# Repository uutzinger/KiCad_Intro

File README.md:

# KiCad Introduction

Created for BME210 Sophomore Design Course

Urs Utzinger, 2026

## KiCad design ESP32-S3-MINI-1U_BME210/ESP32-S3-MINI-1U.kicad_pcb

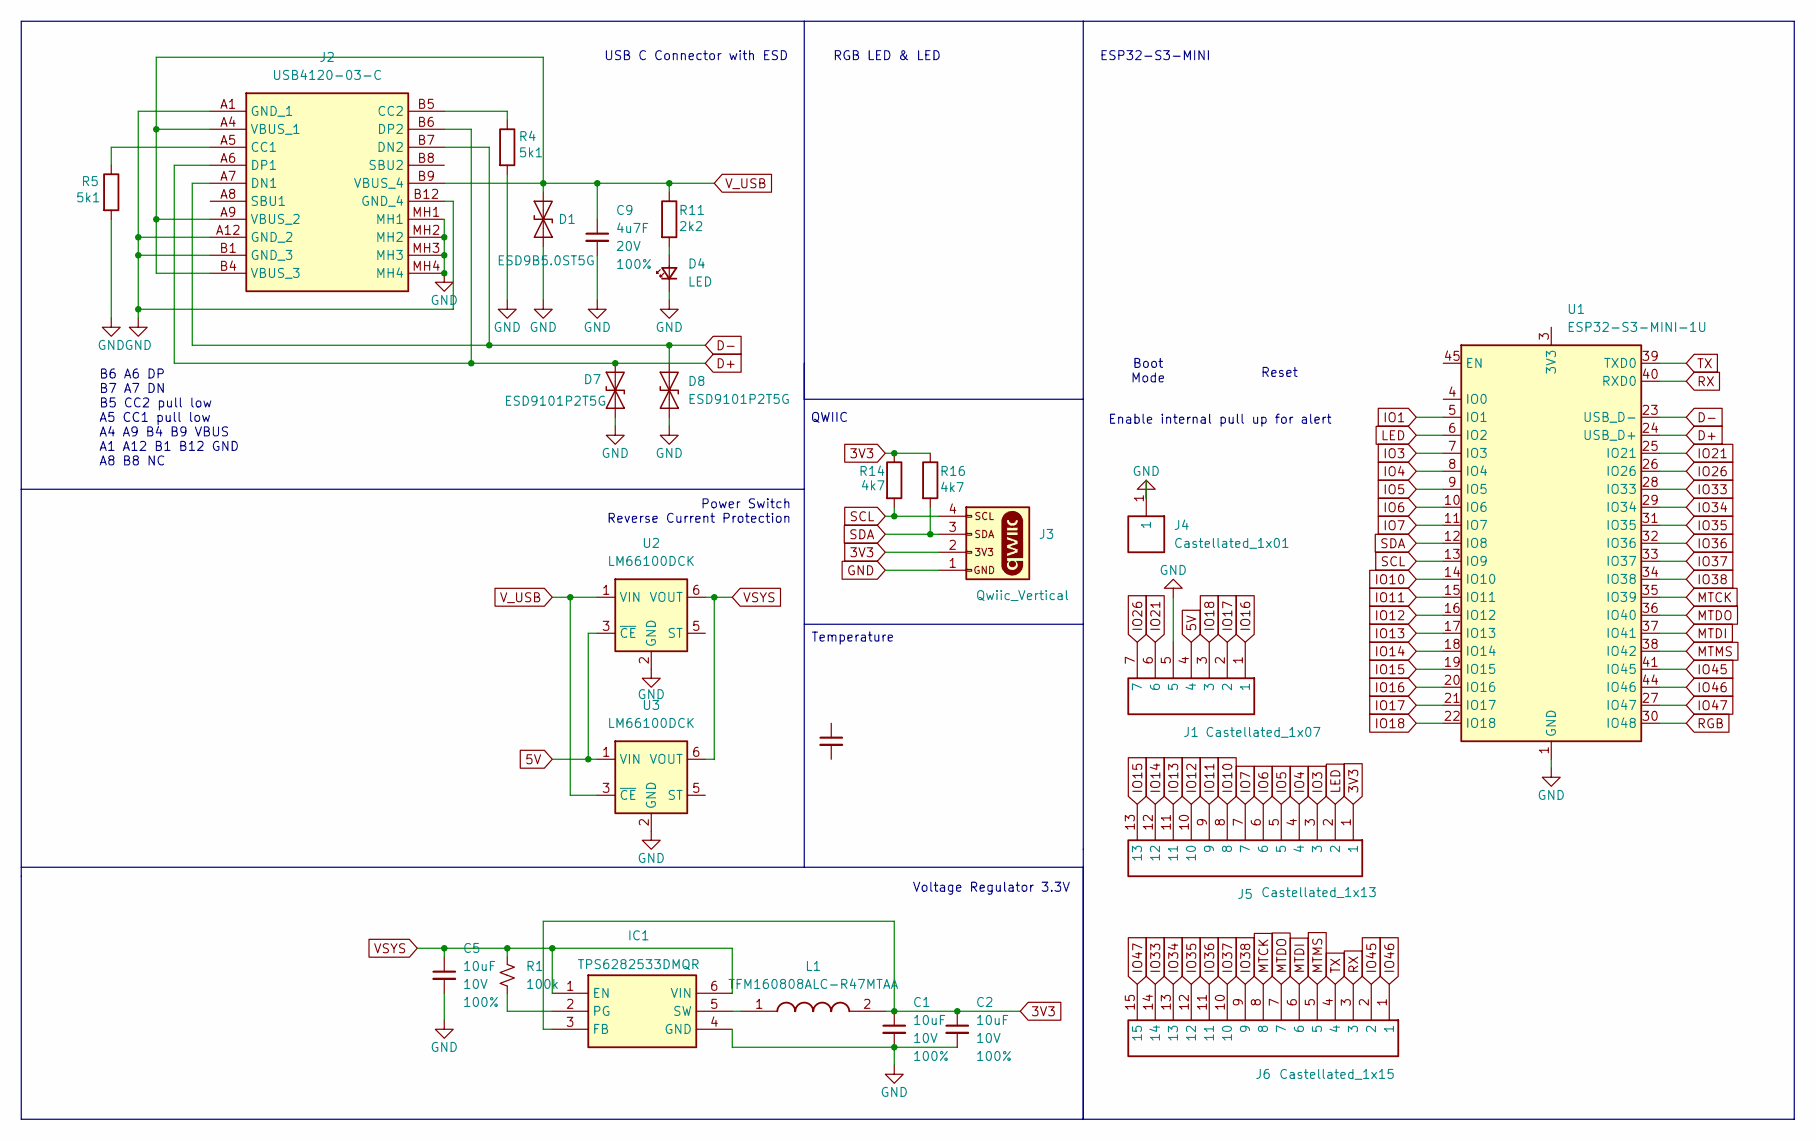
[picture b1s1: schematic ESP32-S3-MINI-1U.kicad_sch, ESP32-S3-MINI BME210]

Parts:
C1, C2, C5: 10uF; C_0402_1005Metric; Voltage 10V; Tolerance 100%
C9: 4u7F; C_0402_1005Metric; Voltage 20V; Tolerance 100%
C14: 10nF; C_0402_1005Metric; Voltage 50V; Tolerance 10%
D1: ESD9B5.0ST5G; D_SOD-923
D4: LED; LED_0402_1005Metric
D7, D8: ESD9101P2T5G; D_SOD-923
IC1: TPS6282533DMQR; Manufacturer_Part_Number TPS6282533DMQR; Mouser Part Number 595-TPS6282533DMQR
J1: Castellated_1x07; Castellated_1x07_P2.54mm_D0.80mm
J2: USB4120-03-C; USB412003C; Manufacturer_Part_Number USB4120-03-C; Mouser Part Number 640-USB4120-03-C
J3: Qwiic_Vertical; JST_1x04_P1.0mm_Vertical_SMD
J4: Castellated_1x01; Castellated_1x01_P2.54mm_D0.80mm
J5: Castellated_1x13; Castellated_1x13_P2.54mm_D0.80mm
J6: Castellated_1x15; Castellated_1x15_P2.54mm_D0.80mm
L1: TFM160808ALC-R47MTAA; INDC1608X75N; Manufacturer_Part_Number TFM160808ALC-R47MTAA; Mouser Part Number 810-TFM160808ALCR47A
R1: 100k; R_0402_1005Metric
R4, R5: 5k1; R_0402_1005Metric
R11: 2k2; R_0402_1005Metric
R14, R16: 4k7; R_0402_1005Metric
U1: ESP32-S3-MINI-1U; ESP32-S2-MINI-1U
U2, U3: LM66100DCK; SOT-363_SC-70-6

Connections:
3V3: C1.1, C2.1, IC1.3 (FB), J3.2, J5.1, L1.2, R14.1, R16.1
5V: J1.4, U2.3 (~CE), U3.1 (VIN)
D+: D7.2 (A2), J2.A6 (DP1), J2.B6 (DP2), U1.24 (USB_D+)
D-: D8.2 (A2), J2.A7 (DN1), J2.B7 (DN2), U1.23 (USB_D-)
GND: C1.2, C2.2, C5.2, C9.2, D1.1 (A1), D4.1 (K), D7.1 (A1), D8.1 (A1), IC1.4 (GND), J1.5, J2.A1 (GND_1), J2.A12 (GND_2), J2.B1 (GND_3), J2.B12 (GND_4), J2.MH1, J2.MH2, J2.MH3, J2.MH4, J3.1, J4.1, R4.2, R5.2, U1.1 (GND), U1.2 (GND), U1.42 (GND), U1.43 (GND), U1.46 (GND), U1.47 (GND), U1.48 (GND), U1.49 (GND), U1.50 (GND), U1.51 (GND), U1.52 (GND), U1.53 (GND), U1.54 (GND), U1.55 (GND), U1.56 (GND), U1.57 (GND), U1.58 (GND), U1.59 (GND), U1.60 (GND), U1.61 (GND), U1.62 (GND), U1.63 (GND), U1.64 (GND), U1.65 (GND), U2.2 (GND), U3.2 (GND)
IO1: U1.5 (IO1)
IO3: J5.3, U1.7 (IO3)
IO4: J5.4, U1.8 (IO4)
IO5: J5.5, U1.9 (IO5)
IO6: J5.6, U1.10 (IO6)
IO7: J5.7, U1.11 (IO7)
IO10: J5.8, U1.14 (IO10)
IO11: J5.9, U1.15 (IO11)
IO12: J5.10, U1.16 (IO12)
IO13: J5.11, U1.17 (IO13)
IO14: J5.12, U1.18 (IO14)
IO15: J5.13, U1.19 (IO15)
IO16: J1.1, U1.20 (IO16)
IO17: J1.2, U1.21 (IO17)
IO18: J1.3, U1.22 (IO18)
IO21: J1.6, U1.25 (IO21)
IO26: J1.7, U1.26 (IO26)
IO33: J6.14, U1.28 (IO33)
IO34: J6.13, U1.29 (IO34)
IO35: J6.12, U1.31 (IO35)
IO36: J6.11, U1.32 (IO36)
IO37: J6.10, U1.33 (IO37)
IO38: J6.9, U1.34 (IO38)
IO45: J6.2, U1.41 (IO45)
IO46: J6.1, U1.44 (IO46)
IO47: J6.15, U1.27 (IO47)
LED: J5.2, U1.6 (IO2)
MTCK: J6.8, U1.35 (IO39)
MTDI: J6.6, U1.37 (IO41)
MTDO: J6.7, U1.36 (IO40)
MTMS: J6.5, U1.38 (IO42)
unnamed: D4.2 (A), R11.2
unnamed: IC1.2 (PG), R1.1
unnamed: IC1.5 (SW), L1.1
unnamed: J2.A5 (CC1), R5.1
unnamed: J2.B5 (CC2), R4.1
RGB: U1.30 (IO48)
RX: J6.3, U1.40 (RXD0)
SCL: J3.4, R14.2, U1.13 (IO9)
SDA: J3.3, R16.2, U1.12 (IO8)
TX: J6.4, U1.39 (TXD0)
VSYS: C5.1, IC1.1 (EN), IC1.6 (VIN), R1.2, U2.6 (VOUT), U3.6 (VOUT)
V_USB: C9.1, D1.2 (A2), J2.A4 (VBUS_1), J2.A9 (VBUS_2), J2.B4 (VBUS_3), J2.B9 (VBUS_4), R11.1, U2.1 (VIN), U3.3 (~CE)

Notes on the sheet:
Voltage Regulator 3.3V
Boot Mode
ESP32-S3-MINI
Power Switch Reverse Current Protection
Temperature
RGB LED & LED
Reset
Enable internal pull up for alert
B6 A6 DP B7 A7 DN B5 CC2 pull low A5 CC1 pull low A4 A9 B4 B9 VBUS A1 A12 B1 B12 GND A8 B8 NC
USB C Connector with ESD
QWIIC

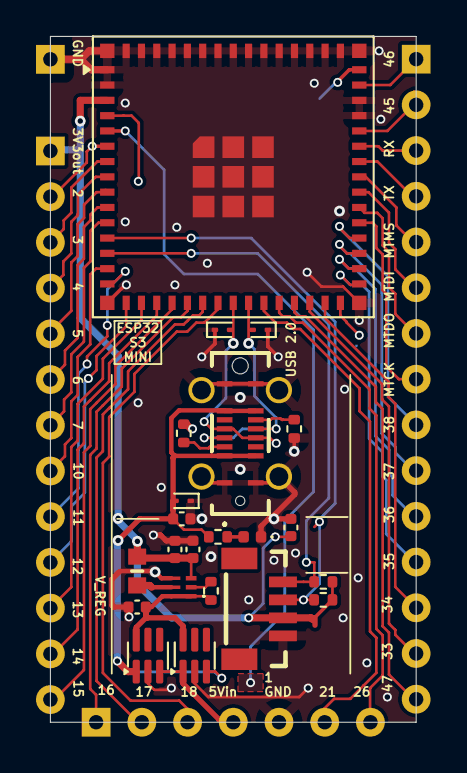
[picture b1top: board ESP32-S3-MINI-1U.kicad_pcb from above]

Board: 2 copper layers, 20.3 x 38.1 mm, 26 parts (0 on the bottom side), 46 nets.

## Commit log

2026-02-19 Update project title in README
2026-02-19 Release
2026-02-19 Add introduction and author information to README
2026-03-17 Missing ESP sym
